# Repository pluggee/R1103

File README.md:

# R1103
Raspberry Pi connector interface

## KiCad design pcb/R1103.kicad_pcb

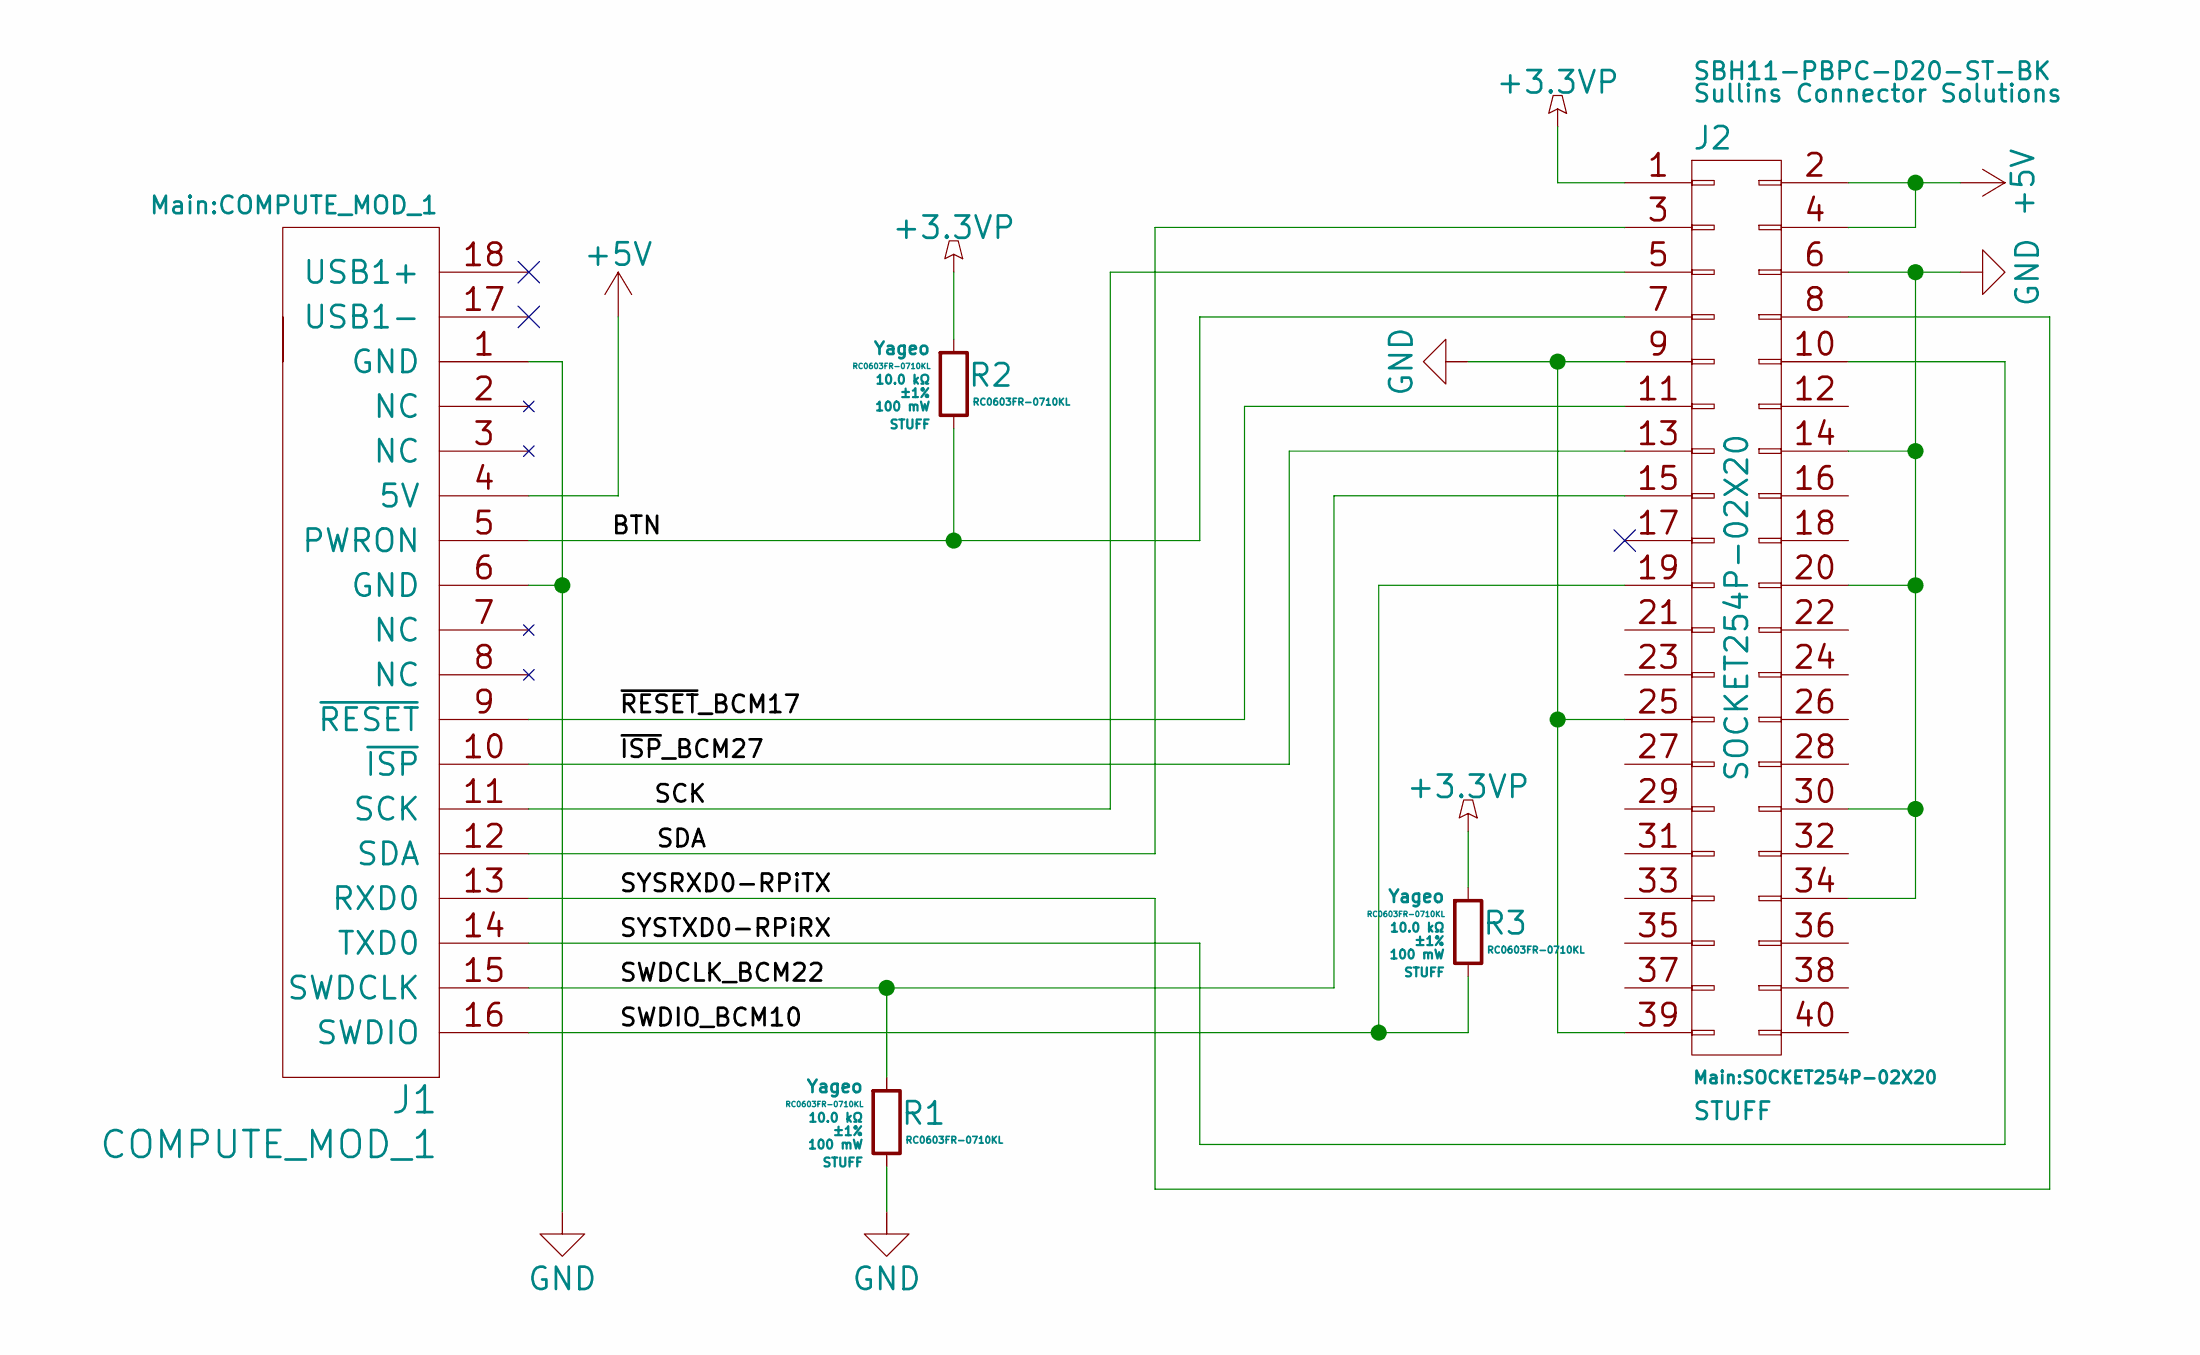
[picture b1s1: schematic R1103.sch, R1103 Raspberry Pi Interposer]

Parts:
J1: COMPUTE_MOD_1
J2: SOCKET254P-02X20; MPN SBH11-PBPC-D20-ST-BK
R1, R2, R3: RC0603FR-0710KL; RESC0603; MPN RC0603FR-0710KL

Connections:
+3.3VP: J2.1, R2.1, R3.1
+5V: J1.4 (5V), J2.2, J2.4
/BTN: J1.5 (PWRON), J2.7, R2.2
/SCK: J1.11 (SCK), J2.5
/SDA: J1.12 (SDA), J2.3
/SWDCLK_BCM22: J1.15 (SWDCLK), J2.15, R1.1
/SWDIO_BCM10: J1.16 (SWDIO), J2.19, R3.2
/SYSRXD0-RPiTX: J1.13 (RXD0), J2.8
/SYSTXD0-RPiRX: J1.14 (TXD0), J2.10
/~ISP~_BCM27: J1.10 (~ISP), J2.13
/~RESET~_BCM17: J1.9 (~RESET), J2.11
GND: J1.1 (GND), J1.6 (GND), J2.6, J2.9, J2.14, J2.20, J2.25, J2.30, J2.34, J2.39, R1.2

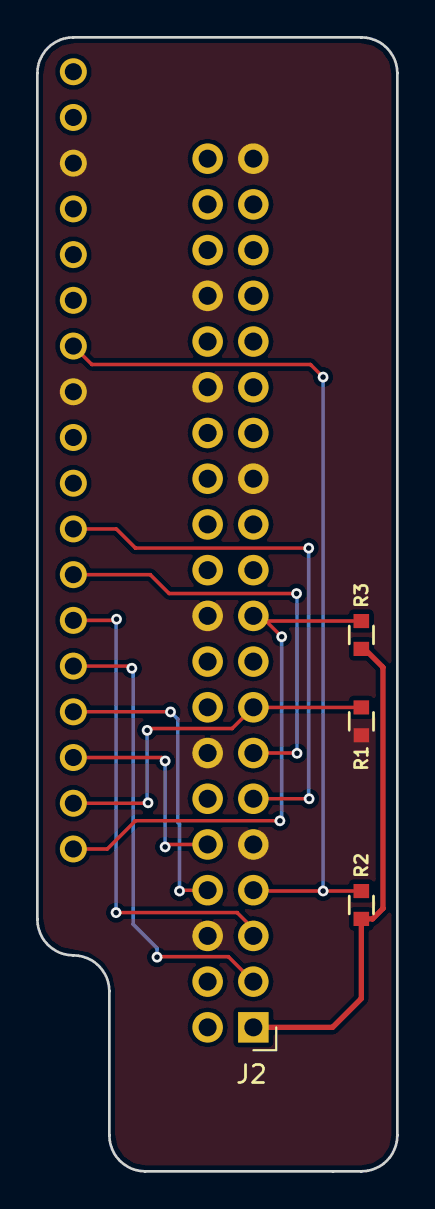
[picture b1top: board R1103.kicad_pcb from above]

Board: 2 copper layers, 20.0 x 63.0 mm, 5 parts (1 on the bottom side), 12 nets.

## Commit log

2017-10-31 adjusted layout to better fit RPi zero W
